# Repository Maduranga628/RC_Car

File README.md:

# RC_Car
Radio Controlled Toy Car's Main PCB

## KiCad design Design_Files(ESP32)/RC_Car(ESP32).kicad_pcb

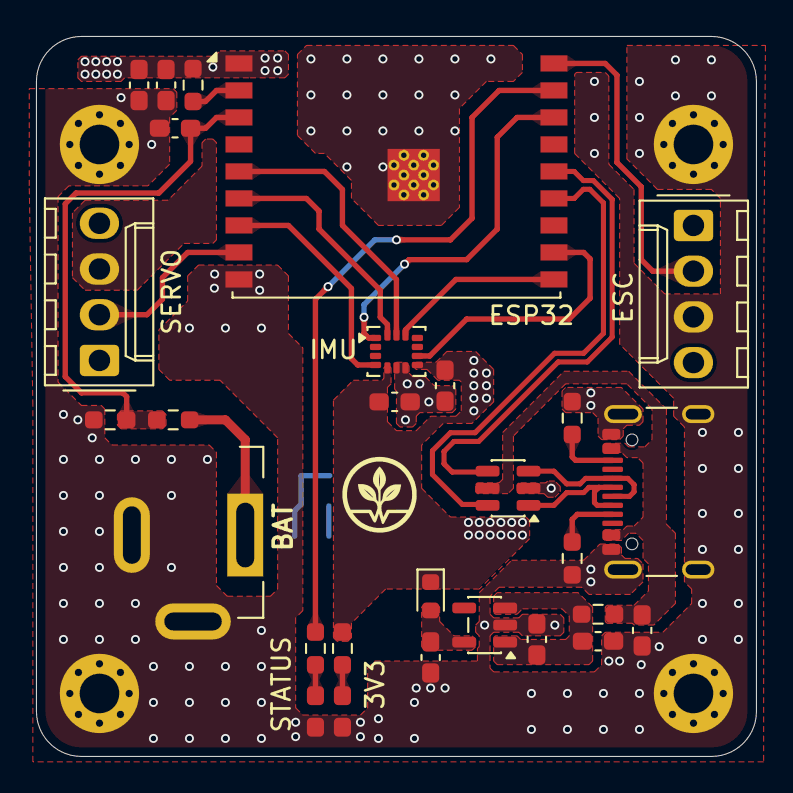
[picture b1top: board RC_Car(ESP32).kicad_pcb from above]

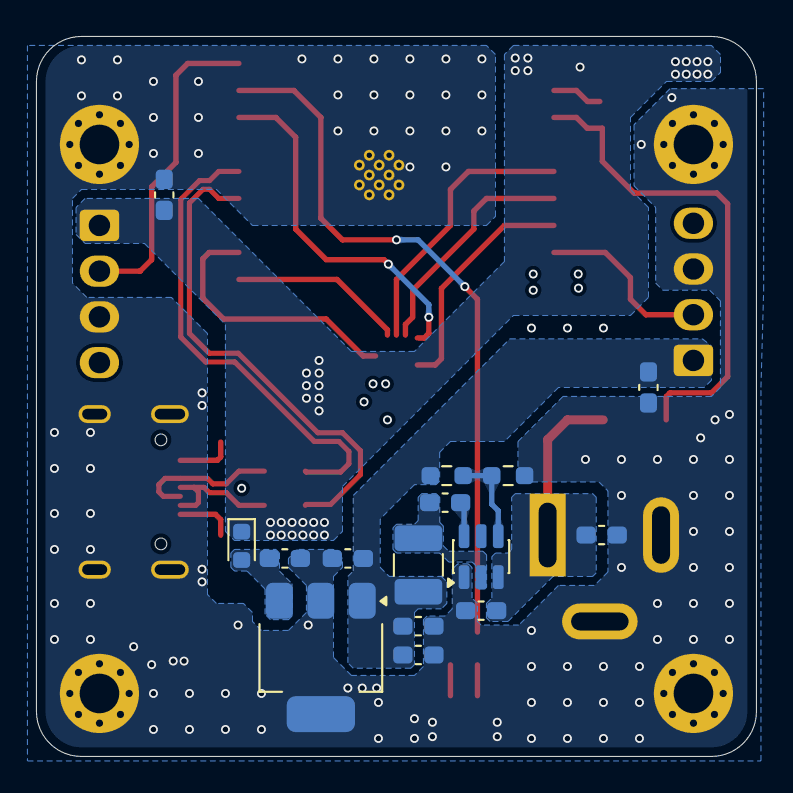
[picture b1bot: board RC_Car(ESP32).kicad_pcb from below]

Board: 4 copper layers, 40.0 x 40.0 mm, 47 parts (15 on the bottom side), 30 nets.

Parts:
3V3: LED; LED_0603_1608Metric_Pad1.05x0.95mm_HandSolder
500mA: TLV75533PDBV; SOT-23-5
BAT: Barrel_Jack_Switch; BarrelJack_GCT_DCJ200-10-A_Horizontal
C1, C10, C11, C12, C13, C14, C16, C18: 100n; C_0603_1608Metric_Pad1.08x0.95mm_HandSolder
C2, C5, C6, C7, C8, C15, C17: 10u; C_0603_1608Metric_Pad1.08x0.95mm_HandSolder
C3, C4, C9: 22u; C_0603_1608Metric_Pad1.08x0.95mm_HandSolder
D1, D2: CDBU70-HF; D_0603_1608Metric
ESC: Conn_01x04; Molex_KK-254_AE-6410-04A_1x04_P2.54mm_Vertical
ESP32: ESP32-C3-WROOM-02
IMU: LSM6DSL; LGA-14_3x2.5mm_P0.5mm_LayoutBorder3x4y
J1: USB_C; USB_C_Receptacle_GCT_USB4105-xx-A_16P_TopMnt_Horizontal
L1: 3u3; L_1210_3225Metric_Pad1.42x2.65mm_HandSolder
MH1, MH2, MH3, MH4: MountingHole_Pad; MountingHole_2.2mm_M2_Pad_Via
R1: 47k5; R_0603_1608Metric_Pad0.98x0.95mm_HandSolder
R2: 52k3; R_0603_1608Metric_Pad0.98x0.95mm_HandSolder
R3: 8k2; R_0603_1608Metric_Pad0.98x0.95mm_HandSolder
R4: 10k; R_0603_1608Metric_Pad0.98x0.95mm_HandSolder
R5: 0R; R_0603_1608Metric_Pad0.98x0.95mm_HandSolder
R6, R7, R8, R9: 5k1; R_0603_1608Metric_Pad0.98x0.95mm_HandSolder
R10: 100R; R_0603_1608Metric_Pad0.98x0.95mm_HandSolder
SERVO: Conn_01x04; Molex_KK-254_AE-6410-04A_1x04_P2.54mm_Vertical
STATUS: LED; LED_0603_1608Metric_Pad1.05x0.95mm_HandSolder
U1: AP62301Z6-7; TSOT-23-6
U2: AZ1117CH2-3.3; SOT-223-3_TabPin2
U4: USBLC6-2SC6; SOT-23-6

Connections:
+3V3A: C10.1, C11.1, C14.1, C15.1, C18.1, D1.1 (K), D2.1 (K), ESC.1, ESP32.1 (3V3), IMU.5 (VDDIO), IMU.8 (VDD), R6.2, R9.2
+3V3_1: C9.1, D2.2 (A), U2.3 (OUT)
+3V3_2: 500mA.5 (OUT), C7.1, D1.2 (A)
+5V: C3.1, C4.1, C8.1, C17.1, L1.2, R2.1, SERVO.1, U2.1 (IN)
+VBUS: C12.1, J1.A4 (VBUS), J1.A9 (VBUS), J1.B4 (VBUS), J1.B9 (VBUS), R5.1, U4.5 (VBUS)
+VBUSF: 500mA.1 (IN), 500mA.3 (EN), C6.1, C13.1, R5.2
+VCC: BAT.1, C2.1, C5.1, R1.2, U1.3 (IN)
/Schematic/BAT_SENSE: C16.1, ESP32.3 (IO4), R1.1, R3.2
/Schematic/BST: C1.1, U1.6 (BST)
/Schematic/BUCKOUT: C1.2, L1.1, U1.2 (SW)
/Schematic/CC1: J1.A5 (CC1), R8.2
/Schematic/CC2: J1.B5 (CC2), R7.2
/Schematic/EN: ESP32.2 (EN), R6.1
/Schematic/ESC_PWM: ESC.2, ESP32.18 (IO0)
/Schematic/FB: R2.2, R4.1, U1.4 (FB)
/Schematic/IMU_CLK: ESP32.5 (IO6), IMU.13 (SCL)
/Schematic/IMU_CS: ESP32.10 (IO10), IMU.12 (CS)
/Schematic/IMU_INT1: ESP32.7 (IO8), IMU.4 (INT1)
/Schematic/IMU_INT2: ESP32.11 (IO20/RXD), IMU.9 (INT2)
/Schematic/IMU_MISO: ESP32.16 (IO2), IMU.1 (SDO/SA0)
/Schematic/IMU_MOSI: ESP32.6 (IO7), IMU.14 (SDA)
/Schematic/PWR_LED: 3V3.2 (A), R9.1
/Schematic/SERVO_PWM: ESP32.8 (IO9), SERVO.2
/Schematic/STATUS: ESP32.17 (IO1), R10.2
/Schematic/STATUS_LED: R10.1, STATUS.2 (A)
/Schematic/USBD+: J1.A6 (D+), J1.B6 (D+), U4.3 (I/O2)
/Schematic/USBD-: J1.A7 (D-), J1.B7 (D-), U4.1 (I/O1)
/Schematic/USB_D+: ESP32.14 (IO19), U4.4 (I/O2)
/Schematic/USB_D-: ESP32.13 (IO18), U4.6 (I/O1)
GND: 3V3.1 (K), 500mA.2 (GND), BAT.2, BAT.3, C2.2, C3.2, C4.2, C5.2, C6.2, C7.2, C8.2, C9.2, C10.2, C11.2, C12.2, C13.2, C14.2, C15.2, C16.2, C17.2, C18.2, ESC.3, ESP32.9 (GND), ESP32.19 (GND), IMU.6 (GND), IMU.7 (GND), J1.A1 (GND), J1.A12 (GND), J1.B1 (GND), J1.B12 (GND), J1.S1 (SHIELD), MH1.1, MH2.1, MH3.1, MH4.1, R3.1, R4.2, R7.1, R8.1, SERVO.3, STATUS.1 (K), U1.1 (GND), U2.2 (GND), U4.2 (GND)

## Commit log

2025-12-04 Create temp
